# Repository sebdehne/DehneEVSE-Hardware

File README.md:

# DehneEVSE Open source EV Charging Station - Hardware

KiCad design files of a controller board for Type-2 charging (IEC 61851) of EVs.

See [Schematic](Media/schematic.pdf) and [3d-view](Media/PCB-3d-view.png).

See [DehneEVSE EV Charging Station](https://dehnes.com/electronics/2021/03/31/dehneevse_charging_station.html) for more 
information on the entire setup.

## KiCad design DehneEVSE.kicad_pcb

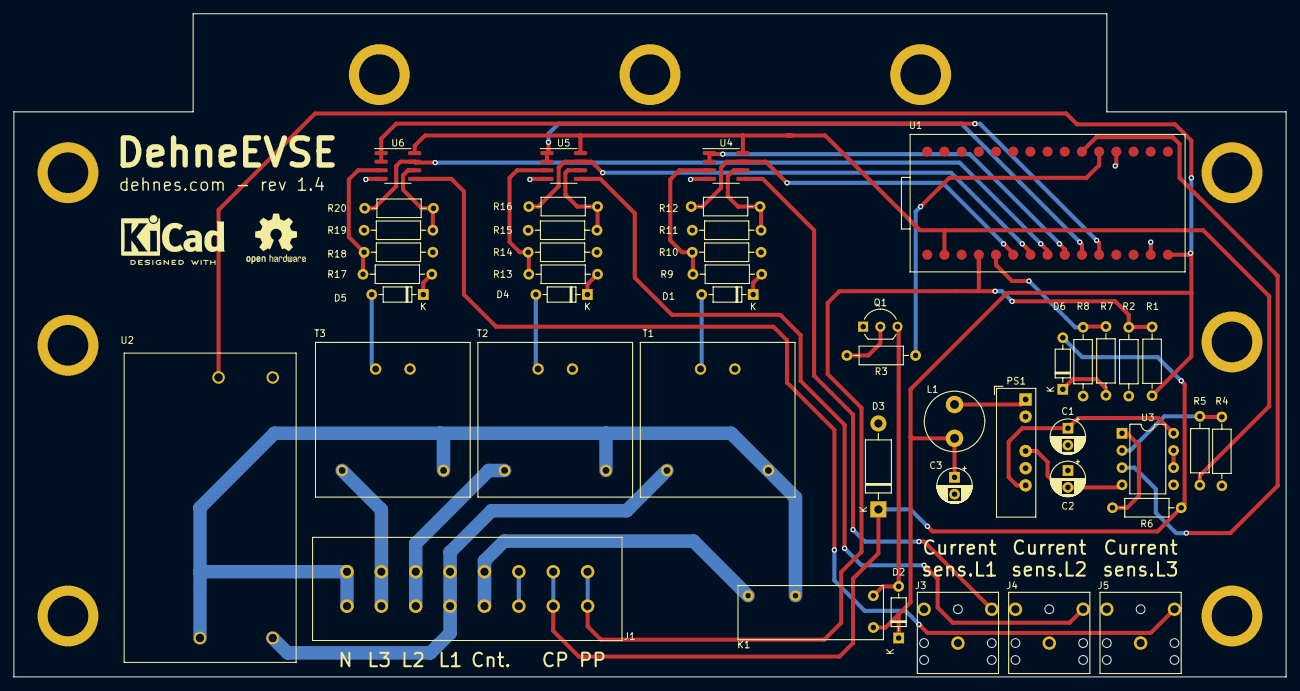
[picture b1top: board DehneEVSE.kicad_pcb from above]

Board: 2 copper layers, 188.0 x 98.0 mm, 46 parts (0 on the bottom side), 43 nets.

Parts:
C1, C2: 1uf; CP_Radial_D5.0mm_P2.50mm
C3: 2.2uf/50V; CP_Radial_D5.0mm_P2.50mm
D1, D2, D4, D5, D6: 1N4148; D_DO-35_SOD27_P7.62mm_Horizontal
D3: TVS-P6KE16CA; D_DO-15_P12.70mm_Horizontal
J1: Connector1; conn_08x02_wago
J3, J4, J5: FC68131; CLIFF_FC68131
K1: G5NB-1A Relay 5VDC; Omron-GSNB-1A
L1: 18uH; L_Radial_D8.7mm_P5.00mm_Fastron_07HCP
PS1: NMA0512SC; Converter_DCDC_XP_POWER-IAxxxxS_THT
Q1: PN2222A; TO-92_Inline_Wide
R1, R2, R6: 1k; R_Axial_DIN0207_L6.3mm_D2.5mm_P10.16mm_Horizontal
R3: 330; R_Axial_DIN0207_L6.3mm_D2.5mm_P10.16mm_Horizontal
R4, R5: 120k; R_Axial_DIN0207_L6.3mm_D2.5mm_P10.16mm_Horizontal
R7: 180k; R_Axial_DIN0207_L6.3mm_D2.5mm_P10.16mm_Horizontal
R8: 47k; R_Axial_DIN0207_L6.3mm_D2.5mm_P10.16mm_Horizontal
R9, R13, R17: 100k; R_Axial_DIN0207_L6.3mm_D2.5mm_P10.16mm_Horizontal
R10, R11, R12, R14, R15, R16, R18, R19, R20: 10k; R_Axial_DIN0207_L6.3mm_D2.5mm_P10.16mm_Horizontal
T1, T2, T3: VB_05-1-12
U1: Arduino Nano 33 IoT; Arduino_Nano_33_iot__SMT
U2: NMA0512SC; CONV_IRM-05-5
U3: LT1498IN8; DIP-8_W7.62mm
U4, U5, U6: MCP602T; SOIC-8_3.9x4.9mm_P1.27mm

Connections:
+3V3: R5.2, U1.2, U4.8, U5.8, U6.8
+5V: C3.1, D2.1, K1.4, L1.2, R1.2, U1.15, U2.VPOS
+12VDC: C1.1, PS1.6, U3.8
-12VDC: C2.2, PS1.4, U3.4
/PP: J1.8, R1.1, R2.2, U1.4
CP: D3.1, D6.2, J1.7, R6.1
CP_READ: R7.1, R8.2, U1.5
CURRENT_SENS_L1_READ: R12.2, U1.6, U4.7
CURRENT_SENS_L2_READ: R16.2, U1.7, U5.7
CURRENT_SENS_L3_READ: R20.2, U1.8, U6.7
CUR_SENS_L1: J3.5, U4.5
CUR_SENS_L2: J4.5, U5.5
CUR_SENS_L3: J5.5, U6.5
Contactor: J1.5, K1.3
DC_RELAY: R3.1, U1.20
GND: C1.2, C2.1, C3.2, D3.2, J3.1, J4.1, J5.1, PS1.2, PS1.5, Q1.1, R2.1, R4.1, R8.1, R10.2, R11.1, R14.2, R15.1, R18.2, R19.1, T1.4, T2.4, T3.4, U1.14, U1.19, U2.VNEG, U3.5, U4.4, U5.4, U6.4
MAINS_L1: J1.4, T1.1, U2.AC/L
MAINS_L2: J1.3, T2.1
MAINS_L3: J1.2, T3.1
MAINS_N: J1.1, K1.2, T1.2, T2.2, T3.2, U2.AC/N
unnamed: D1.1, R9.1
unnamed: D1.2, T1.3
unnamed: D2.2, K1.1, Q1.3
unnamed: D4.1, R13.1
unnamed: D4.2, T2.3
unnamed: D5.1, R17.1
unnamed: D5.2, T3.3
unnamed: D6.1, R7.2
unnamed: L1.1, PS1.1
unnamed: Q1.2, R3.2
unnamed: R4.2, R5.1, U3.2
unnamed: R6.2, U3.1
unnamed: R9.2, R10.1, U4.3
unnamed: R11.2, R12.1, U4.6
unnamed: R13.2, R14.1, U5.3
unnamed: R15.2, R16.1, U5.6
unnamed: R17.2, R18.1, U6.3
unnamed: R19.2, R20.1, U6.6
unnamed: U3.6, U3.7
PWM: U1.21, U3.3
VOLTAGE_SENS_L1_READ: U1.9, U4.1, U4.2
VOLTAGE_SENS_L2_READ: U1.10, U5.1, U5.2
VOLTAGE_SENS_L3_READ: U1.11, U6.1, U6.2

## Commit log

2021-02-21 revision 1
2021-02-21 schematic pdf
2021-02-22 changed drill holes for 3.5mm minijack connector
2021-02-22 revision 1.2 - added connection to PE
2021-02-25 Create LICENSE
2021-02-28 Updated some resistor values & Readme
2021-03-03 Working on revision 1.3
2021-03-08 PCB layout for rev 1.3
2021-03-10 revision 1.3 done
2021-03-11 renamed to DehneEVSE
2021-03-11 minor updates
2021-03-13 updated footprint arduino
2021-03-20 rev 1.4
2021-03-21 rev 1.4 - README.md
2021-03-21 rev 1.4 - printout
2021-04-01 readme updated
